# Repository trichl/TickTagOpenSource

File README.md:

# I Repository Introduction
This repository contains the entire production-ready design (hardware, software, user interface, 3D-printable housing, assembly instructions) of the open-source TickTag GPS logger.

# II Hardware Production
* See sub folder [TickTagHardware](TickTagHardware)
* Schematics (.sch) and boards (.brd) are designed in Autodesk Eagle 9.5.2
* PCBs were produced and assembled by [PCBWay](https://www.pcbway.com) (production-ready Gerber files and PCBWay settings in [TickTagHardware/GerberProductionFiles](TickTagHardware/GerberProductionFiles))
* Production settings:
   * **REV3**: 24.9 x 10.5 mm, 2 layers, 0.15 mm thickness (flex), 0.35 mm min hole size, immersion gold (ENIG) surface finish (1U"), 0.06 mm min track spacing, 1 oz Cu finished copper, polyimide flex material

   * **REV4**: 23.61 x 10.06 mm, 2 layers, 0.2 mm thickness, 0.25 mm min hole size, immersion gold (ENIG) surface finish (1U"), tenting vias, 5/5 mil min track spacing, 1 oz Cu finished copper, FR-4 TG150 material

   * **User interface board**: 66.4 x 17.8 mm, 2 layers, 1 mm thickness, 0.3 mm min hole size, immersion gold (ENIG) surface finish (1U"), tenting vias, 6/6 mil min track spacing, 1 oz Cu finished copper, FR-4 TG130 material
* Differences between REV3 and REV4:
   * 0.2 mm PCB instead of 0.15 mm (more robust)
   * PCB slots instead of pads for soldering LiPos directly to the PCB
   * New load switch (SiP32431DNP3-T1GE4), as the old load switch has long lead times
   * Reduced the footprint sizes of some of the capacitors and resistors from 0402 to 0201

# III Programming and Assembly

## IDE for Software Development (Windows)
* Atmel Studio 7.0: https://www.microchip.com/en-us/tools-resources/develop/microchip-studio
* Programming language: C / C++

## Android App
* Developed in Android Studio 3.5.1: https://developer.android.com/studio

## Using an Arduino Nano for Flashing
* Follow the instructions on https://github.com/ElTangas/jtag2updi
* The 4.7k resistor is already integrated on the user interface board and does not need to be added
* Alternatively software can be flashed with the official Atmel-ICE: https://www.microchip.com/en-us/development-tool/ATATMEL-ICE

## Flashing the Firmware
Flashing should be done before soldering a battery to the tag.

1. Check if the yellow jumper (E) connects "1" and "2" ("ldo")
2. Gently click the tag on the user interface board (without battery attached to it) (A), mind the correct orientation of the tag
3. Connect D6 of the Arduino Nano to the UPDI pin of the user interface board (or use an Atmel-ICE instead of an Arduino Nano)
4. Connect the user interface board to a computer (red LED turns on) (G), connect the Arduino Nano to the same computer
5. Slide the UPDI button on the user interface board (H) to ON
6. Go to [TickTagProgramming/avrdude](TickTagProgramming/avrdude), open ScriptWriteFuses_ATTINY1626.bat (or ScriptWriteFuses_ATTINY1616.bat, if you use the 1616) with a text editor and enter the COM port of the Arduino Nano on your computer
7. Execute ScriptWriteFuses_ATTINY1626.bat to write the configuration fuses of the ATTINY.
( It may be possible that executing the script raises an error ie. missing dll file. In this case, try to download and install WinAVR [here](https://sourceforge.net/projects/winavr/) )
8. Open Atmel Studio 7.0 and load the project [TickTagSoftwareBurst](TickTagSoftwareBurst) (you might need to setup the project first, and set the current device to ATtiny1626)
9.  
    1.  Configure the ATTINY programming via Arduino Nano under Tools -> External Tools
    2.  To choose the command, select the three dots and find the location of the TickTagOpenSource repository. Then navigate to TickTagProgramming\avrdude\bin and select avrdude.exe
    3.  For the Arguments: "-P COM7 -c jtag2updi -p t1626 -U flash:w:$(ProjectDir)Debug\\$(TargetName).hex:i", COM7 needs to be replaced with the COM port of the Arduino Nano:

10. Press F7 to compile the firmware
11. Press Tools -> jtag2updi ATtiny1626 to flash the firmware

## Tag Assembly

* If the firmware is successfully flashed onto the microcontroller you can solder a battery to the TickTag battery terminals (plus and minus is written on the tag)
* No battery protection circuit is needed, the battery is protected by software
* You can use a glass fiber pen to roughen the LiPo tabs, which makes soldering of the aluminium tabs more easy (e.g., with a Laeufer 69119 pen)
* Keep the soldering work on the LiPo very short, otherwise the battery might be damaged due to high temperatures
* Keep the area below the TickTag as flat as possible, otherwise you might not be able to click the tag on the user interface board anymore

# IV Tag Manual

## Charging the Battery
**WARNING**: never connect the TickTag to the user interface board when the 3-pin jumper is set to "ldo", otherwise the LiPo will be damaged permanently. The battery can be recharged directly on the breakout board:

1. Check if the yellow jumper connects (E) "3" and "2" ("lipo")
2. Gently click the tag on the user interface board (with battery attached to it) (A), mind the correct orientation of the tag
3. Connect the USB connector to a computer or powerbank (red LED turns on) (G)
4. Slide the charge button on the user interface board (F) to the left (ON)
5. A green LED on the user interface board turns on and indicates that the battery is being charged
6. In case the tag was previously activated, it first needs to be deactivated:
   * Wait some minutes until battery is charged a bit
   * Press the white button (D) for 5 seconds to restart the tag and enter menue
   * Green LED on the tag will blink 5 times to indicate download mode and system restart
7. Wait until the green LED on the user interface board turns off (battery charged)
   * This can take hours (default charge current: 15 mA)
   * For example: an empty 30 mAh lipo battery needs 2 hours to be fully charged
   * For example an empty 120 mAh lipo battery needs 8 hours to be fully charged
8. The tag can be activated again (see chapter "Activation")
   * Warning: If the memory is full the tag can not be reactivated (data download necessary, see chapter "Data Download, Configuration and Memory Reset")

## Activation
* Prerequisites
   * The tags need to be connected to a charged lithium polymer battery (plus and minus pads on the tag are soldered to the battery)
   * If the battery voltage is too low, the tag won’t start (please charge the battery), see chapter "Charge Battery"
   * If the data memory is full, the tag won't start (please download the data and reset the memory), see chapter "Data Download, Configuration and Memory Reset"
   * Check the location of the green LED on the tag (it will give you visual feedback):

### Activation option 1: by a wire

1. Gently touch with one end of a conducting wire the ground connection where the battery minus is soldered to
2. Gently touch with the other end of the wire the hole marked with "A" (or "ST")
3. Once the tag starts blinking green, remove the wire immediately (should not take longer than 2 seconds)
4. The tag blinks 7 times to indicate that it’s activated, then waits for 700 ms and is blinking again to indicate battery status (1 time = battery low, 7 times = battery is full)
5. The green LED is located on the back side of the tag, so it's best to hold the breakout board sideways to see the blinking LED under the tag
6. If it doesn't blink at all: battery voltage might be low or the tag is already activated
7. If the tag blinks 5 times it entered download mode (was already activated), please wait a minute and start again from the beginning
8. The tag is activated and will start sampling GPS data after 10 seconds (default configuration, can be changed, see chapter "Data Download, Configuration and Memory Reset")

### Activation option 2: on breakout board

1. Locate the click connector on the tag (see picture above)
2. Take a look at the breakout board, do not connect the USB power connector (G) to the computer or phone (no external power needed for activation)
3. Gently click the tag on the user interface board (with battery attached to it) (A), mind the correct orientation of the tag
      * Take care of the correct orientation of the tag as shown in the photo, otherwise a short circuit might permanently damage the tag
4. Now press the white button (D) for two seconds until the tag starts to blink
      * Do not press the button longer than some seconds
      * The tag blinks 7 times to indicate that it’s activated, then waits for 700 ms and is blinking again to indicate battery status (1 time = battery low, 7 times = battery is full)
      * The green LED is located on the back side of the tag, so it's best to hold the breakout board sideways to see the blinking LED under the tag
      * If it doesn't blink at all: battery voltage might be low or the tag is already activated
      * If the tag blinks 5 times it entered download mode (was already activated), please wait a minute and start again from the beginning
5. The tag is activated and will start sampling GPS data after 10 seconds (default configuration, can be changed, see chapter "Data Download, Configuration and Memory Reset")

## After the Activation (Data Sampling)
* After the activation delay, the tag starts blinking green every second and tries to get the current time via GPS satellites. If it can’t obtain the time within 120 seconds, it will sleep for 15 minutes and will try again.
   * **IMPORTANT**: If blinking configuration is set to false the tag will completely stop blinking at all after getting the current UTC time
   * If you have configured the tag to only sample GPS at certain times:
       * **IMPORTANT**: Before attaching the tag to the animal (e.g., the day before): go outside, activate the tag, wait until it starts blinking, wait until the green LED stays on for 2 seconds (tag got the time and went to sleep mode).
* The tag samples GPS data (continuously or from time to time, depending on the configuration)
* The module deactivates itself if the battery voltage is low (default configuration: 3.3V) or if the memory is full (maximum 13,100 fixes)

## On-Animal Mounting
* **IMPORTANT**: The small antenna of the TickTag is disturbed by any electrically conducting material nearby, so keep the antenna away from other tags, VHF/UHF tags, batteries, screws or similar materials (at least 5 cm).
* **IMPORTANT**: The antenna can easily break if bent too strong. Try to protect the antenna with a 3D-printed housing (for example with ASA material).
* **IMPORTANT**: The battery needs to be located behind the tag (see picture below), never under the tag, as it will disturb the antenna.
* **IMPORTANT**: Mount the tag on the flat side (connector facing down, top side with antenna facing the sky). The photo shows the top side that should face the sky:

* **IMPORTANT**: Do not glue anything on the connector that can't be removed, otherwise data cannot be downloaded (Bostik Blu Tack is a glue that can be easily removed afterwards):

## Data Download, Configuration and Memory Reset

1. Choose a serial software
   * **Option 1**: Download a serial program for your computer
       * For example (Windows 10): Termite: https://www.compuphase.com/software_termite.htm (see screenshot above for configuration)
       * For example (Windows 10): MobaXTerm: https://mobaxterm.mobatek.net/ (see screenshot above for configuration)
       * The Arduino Serial Monitor also works fine
   * **Option 2**: Use the TickTag Android app [TickTagAndroidApp](TickTagAndroidApp) and an USB OTG adapter to connect the breakout board with the phone
2. The battery needs to be connected (soldered) to the tag
3. Check if the yellow jumper connects (E) "3" and "2" ("lipo")
4. Gently click the tag on the user interface board (with battery attached to it) (A), mind the correct orientation of the tag
5. Connect the USB connector to a computer or Android phone (red LED turns on) (G)
6. Slide the charge button on the user interface board (F) to the left (ON) to charge the battery while downloading data (not mandatory, but recommended)
7. **For option 1**: Open the serial program on your computer with following settings:
   * COM port: select the CP2104N COM port from the list
   * Baud rate: 9600
   * Default serial settings (8 data bits, 1 stop bit, no parity)
8. Click on CONNECT in your serial program or the Android app
9. Press the download button (D) for 5 seconds (not longer) until the green LED on the tag blinks for 5 times
10. Data download is shown in your serial program (in CSV format)
11. After the download the tag shows a little menu for configuration
       * Data download might take some minutes (if memory is full)
       * Data download can be interrupted by pressing the download button once (short), data will not be deleted
12. In the command line of your serial program enter "1" and press return to reset the memory (when using the Android app: press the "Reset memory" button)
13. The tag will confirm that the memory is now empty
14. The tag will restart into the activation state after some time (waiting on tag activation, see chapter "Activation")

Example data output of the serial program (or Android app):

```
---TICK-TAG---
*START MEMORY*
UVs: 0, TOs: 0/0, ErrorsOrGF: 0, TTFF: 68
Fixes: 10, Avg. TTF: 11 s, Avg. HDOP (x10): 16
count,timestamp,lat,lon
1,1635235981,47.74340,8.99910
2,1635236130,47.74346,8.99922
3,1635236352,47.74340,8.99889
4,1635236506,47.74327,8.99894
5,1635236682,47.74336,8.99879
6,1635238092,47.74340,8.99824
7,1635238313,47.74304,8.99896
8,1635238411,47.74329,8.99883
9,1635238511,47.74332,8.99878
10,1635238610,47.74325,8.99881
*END MEMORY*
V201, ID: 30-2509, 3533mV, 01b
SETTINGS:
- Min voltage: 3300 mV
- Frequency: 90 s
- Min HDOP (x10): 30
- Activation delay: 60 s
- Geofencing: 0
- Burst duration: 0 s
- Time: 8:00 - 14:00 UTC

0 Read memory
1 Reset memory
2 Set min. voltage
3 Set frequency
4 Set accuracy
5 Set activation delay
6 Set times
7 Toggle geofencing ON/OFF
8 Set burst duration
9 Exit
```

## Configuration Parameters
* **Read memory**: printing all stored GPS fixes as CSV-compatible list (count, timestamp in UTC, latitude, longitude)
* **Reset memory**: deleting all stored GPS fixes
* **Min. voltage (3000 - 4250, in mV)**: recording is stopped when battery voltage (open-circuit, no load) drops below that threshold
* **Frequency (1 - 16382, in s)**: GPS fix attempt frequency, between 1 and 5 s the TickTag keeps the GPS module constantly powered and puts the device in fitness low power mode
* **Accuracy (1 - 250, HDOP x 10)**: HDOP value (times 10, 30 = 3.0) that tries to be achieved within 9 seconds after getting the first positional estimate
* **Activation delay (10 - 16382, in s)**: delay after activation before the tag starts recording data
* **Sampling times (0000 - 2359, time within day)**: daily recording time window
* **Geo-fencing (true/false)**: if set to true the first GPS fix becomes the home location and only fixes outside a 300 m radius are stored (10 min hibernation afterwards)
* **Blinking (true/false)**: if set to true the tag blinks every second when GPS is active

## Default Configuration
* After flashing the firmware the default configuration is set to:
* **Min. voltage (3000 - 4250, in mV)**: 3000
* **Frequency (1 - 16382, in s)**: 30
* **Accuracy (1 - 250, HDOP x 10)**: 30
* **Activation delay (10 - 16382, in s)**: 10
* **Sampling times (0000 - 2359, time within day)**: always on
* **Geo-fencing (true/false)**: false
* **Blinking (true/false)**: false

## State Machine

# V Data Compression Algorithm
GPS data is stored on the 128 kByte EEPROM with a lossless compression algorithm. GPS positions are stored with 5 decimal places (accuracy: 1.11 m).

* **Latitute (A)**: stored in 25 Bit (unsigned): compressedLatitude = (latitude * 100000) + 9000000
* **Longitude (B)**: stored in 26 Bit (unsigned): compressedLongitude = (longitude * 100000) + 18000000
* **Timestamp (C)**: stored in 29 Bit  (unsigned): compressedTimestamp = timestamp - 1618428394
* Storage pattern of Bits: **AAAAAAAA AAAAAAAA AAAAAAAA ABBBBBBB BBBBBBBB BBBBBBBB BBBCCCCC CCCCCCCC CCCCCCCC CCCCCCCC**
* Total length: 10 Byte per GPS fix

# VI 3D-printed Housings
* Check [TickTag3DPrints](TickTag3DPrints) for .STL files (designed in Fusion 360)
* Housings were printed with ASA filament on a Prusa Mini (0.4 mm nozzle)
* PrusaSlider 2.2.0 settings: 0.45 mm extrusion width, 0.10 mm DETAIL settings

# VII Data
* Check [TickTagData](TickTagData) for data results

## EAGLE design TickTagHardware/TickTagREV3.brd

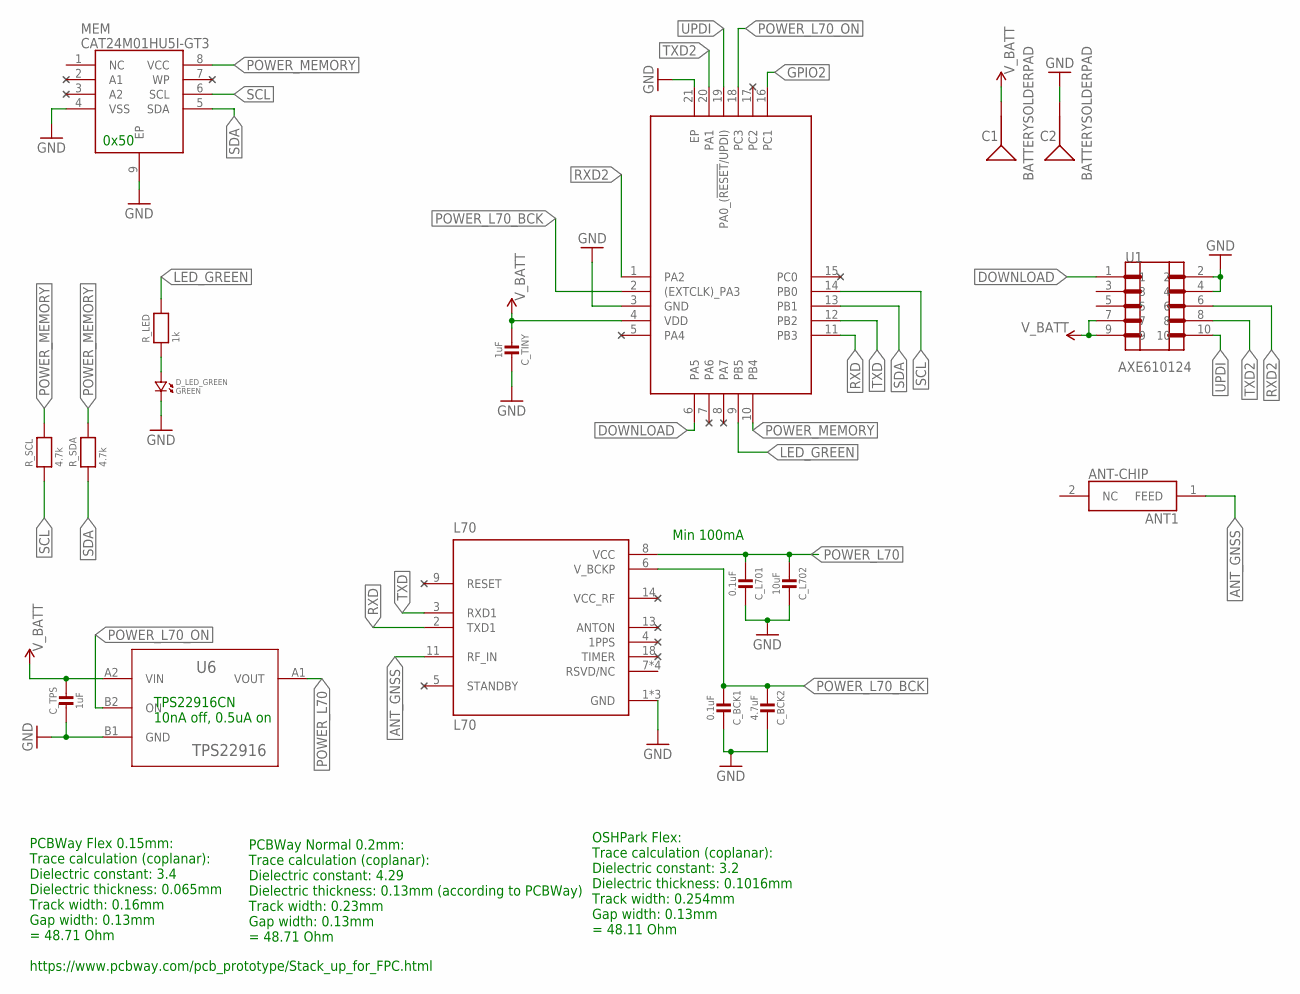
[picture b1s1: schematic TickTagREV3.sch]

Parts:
ANT-CHIP: ANT1; SAMACSYS_PARTS_1575AT43A0040E
ATTINY: ATTINY1616-MFR; QFN40P300X300X90-21N
C1, C2: BATTERYSOLDERPAD
C_BCK1: 0.1uF; MICROBUILDER__0402MP
C_BCK2: 4.7uF; MICROBUILDER__0402MP
C_L701: 0.1uF; MICROBUILDER__0402MP
C_L702: 10uF; MICROBUILDER__0402MP
C_TINY: 1uF; MICROBUILDER__0402MP
C_TPS: 1uF; MICROBUILDER__0402MP
D_LED_GREEN: GREEN; CMONR_STANDARDPARTS_0402.LED
L70: L70; XCVR_L70
MEM: CAT24M01HU5I-GT3; SON50P300X200X55-9N
R_LED: 1k; MICROBUILDER__0402MP
R_SCL: 4.7k; MICROBUILDER__0402MP
R_SDA: 4.7k; MICROBUILDER__0402MP
U1: AXE610124
U6: TPS22916

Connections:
ANT_GNSS: ANT-CHIP.1 (FEED), L70.11 (RF_IN)
DOWNLOAD: ATTINY.6 (PA5), U1.1
GND: ATTINY.3 (GND), ATTINY.21 (EP), C2.1, C_BCK1.1, C_BCK2.1, C_L701.1, C_L702.1, C_TINY.1, C_TPS.2, D_LED_GREEN.P$2 (2), L70.1 (GND), L70.10 (GND), L70.12 (GND), MEM.4 (VSS), MEM.9 (EP), U1.2, U1.4, U6.B1 (GND)
GPIO2: ATTINY.16 (PC1)
LED_GREEN: ATTINY.9 (PB5), R_LED.2
unnamed: D_LED_GREEN.P$1 (1), R_LED.1
POWER_L70: C_L701.2, C_L702.2, L70.8 (VCC), U6.A1 (VOUT)
POWER_L70_BCK: ATTINY.2 ((EXTCLK)_PA3), C_BCK1.2, C_BCK2.2, L70.6 (V_BCKP)
POWER_L70_ON: ATTINY.18 (PC3), U6.B2 (ON)
POWER_MEMORY: ATTINY.10 (PB4), MEM.8 (VCC), R_SCL.2, R_SDA.2
RXD: ATTINY.11 (PB3), L70.2 (TXD1)
RXD2: ATTINY.1 (PA2), U1.6
SCL: ATTINY.14 (PB0), MEM.6 (SCL), R_SCL.1
SDA: ATTINY.13 (PB1), MEM.5 (SDA), R_SDA.1
TXD: ATTINY.12 (PB2), L70.3 (RXD1)
TXD2: ATTINY.20 (PA1), U1.8
UPDI: ATTINY.19 (PA0_(!RESET!/UPDI)), U1.10
V_BATT: ATTINY.4 (VDD), C1.1, C_TINY.2, C_TPS.1, U1.7, U1.9, U6.A2 (VIN)

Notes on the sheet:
0x50
Min 100mA
TPS22916CN 10nA off, 0.5uA on
OSHPark Flex: Trace calculation (coplanar): Dielectric constant: 3.2 Dielectric thickness: 0.1016mm Track width: 0.254mm Gap width: 0.13mm = 48.11 Ohm
PCBWay Flex 0.15mm: Trace calculation (coplanar): Dielectric constant: 3.4 Dielectric thickness: 0.065mm Track width: 0.16mm Gap width: 0.13mm = 48.71 Ohm https://www.pcbway.com/pcb_prototype/Stack_up_for_FPC.html
PCBWay Normal 0.2mm: Trace calculation (coplanar): Dielectric constant: 4.29 Dielectric thickness: 0.13mm (according to PCBWay) Track width: 0.23mm Gap width: 0.13mm = 48.71 Ohm

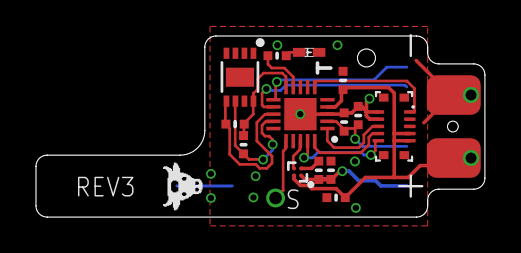
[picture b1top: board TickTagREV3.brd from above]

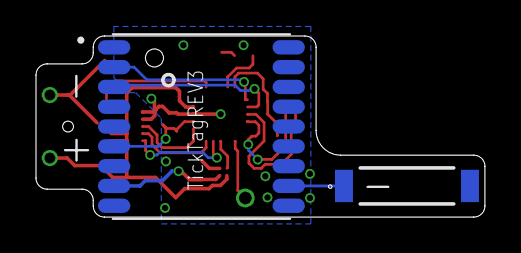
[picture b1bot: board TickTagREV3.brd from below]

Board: 2 copper layers, 24.9 x 10.1 mm, 18 parts (2 on the bottom side), 17 nets.

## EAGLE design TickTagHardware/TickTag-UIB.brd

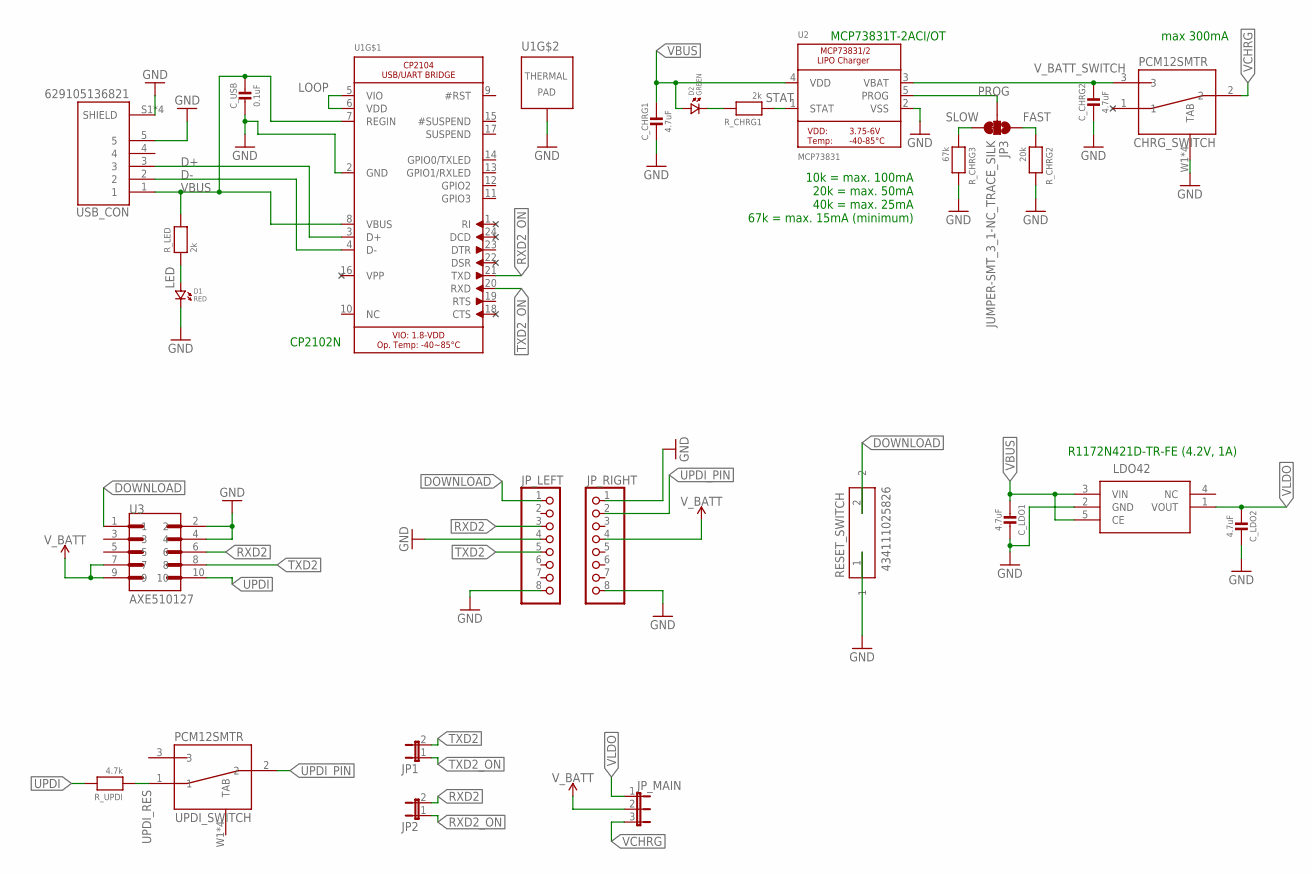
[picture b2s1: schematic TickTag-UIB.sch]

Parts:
CHRG_SWITCH: PCM12SMTR
C_CHRG1, C_CHRG2: 4.7uF; MICROBUILDER__0402MP
C_LDO1, C_LDO2: 4.7uF; MICROBUILDER__0402MP
C_USB: 0.1uF; MICROBUILDER__0402MP
D1: RED; CMONR_STANDARDPARTS_0402.LED
D2: GREEN; CMONR_STANDARDPARTS_0402.LED
JP1, JP2: JP1E; JP1
JP3: JUMPER-SMT_3_1-NC_TRACE_SILK; SMT-JUMPER_3_1-NC_TRACE_SILK
JP_LEFT: PINHD-1X8BIG; 1X08-BIG
JP_MAIN: JP2E; JP2
JP_RIGHT: PINHD-1X8BIG; 1X08-BIG
LDO42: R1172N421D-TR-FE
RESET_SWITCH: 434111025826
R_CHRG1: 2k; MICROBUILDER__0402MP
R_CHRG2: 20k; MICROBUILDER__0402MP
R_CHRG3: 67k; MICROBUILDER__0402MP
R_LED: 2k; MICROBUILDER__0402MP
R_UPDI: 4.7k; MICROBUILDER__0402MP
U1: CP2104_MICROBUILDER_CP2104; CP2104_MICROBUILDER_QFN24_4MM_SMSC
U2: MCP73831; MICROBUILDER_SOT23-5
U3: AXE510127
UPDI_SWITCH: PCM12SMTR
USB_CON: 629105136821; WE_629105136821

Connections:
D+: U1.3 (D+), USB_CON.3
D-: U1.4 (D-), USB_CON.2
DOWNLOAD: JP_LEFT.1, RESET_SWITCH.2, U3.1
FAST: JP3.1, R_CHRG2.1
GND: CHRG_SWITCH.W1 (TAB), CHRG_SWITCH.W2 (TAB), CHRG_SWITCH.W3 (TAB), CHRG_SWITCH.W4 (TAB), C_CHRG1.2, C_CHRG2.2, C_LDO1.1, C_LDO2.1, C_USB.2, D1.P$2 (2), JP_LEFT.4, JP_LEFT.8, JP_RIGHT.1, JP_RIGHT.8, LDO42.2 (GND), RESET_SWITCH.1, R_CHRG2.2, R_CHRG3.2, U1.2 (GND), U1.THERM (TP), U2.2 (VSS), U3.2, U3.4, USB_CON.5, USB_CON.S1 (SHIELD), USB_CON.S2 (SHIELD), USB_CON.S3 (SHIELD), USB_CON.S4 (SHIELD)
LED: D1.P$1 (1), R_LED.1
LOOP: U1.5 (VIO), U1.6 (VDD)
PROG: JP3.2, U2.5 (PROG)
RXD2: JP2.2, JP_LEFT.3, U3.6
RXD2_ON: JP2.1, U1.21 (TXD)
SLOW: JP3.3, R_CHRG3.1
STAT: R_CHRG1.1, U2.1 (STAT)
STAT_BTW: D2.P$2 (2), R_CHRG1.2
TXD2: JP1.2, JP_LEFT.5, U3.8
TXD2_ON: JP1.1, U1.20 (RXD)
UPDI: R_UPDI.2, U3.10
UPDI_PIN: JP_RIGHT.2, UPDI_SWITCH.2
UPDI_RES: R_UPDI.1, UPDI_SWITCH.1
VBUS: C_CHRG1.1, C_LDO1.2, C_USB.1, D2.P$1 (1), LDO42.3 (VIN), LDO42.5 (CE), R_LED.2, U1.7 (REGIN), U1.8 (VBUS), U2.4 (VDD), USB_CON.1
VCHRG: CHRG_SWITCH.2, JP_MAIN.3
VLDO: C_LDO2.2, JP_MAIN.1, LDO42.1 (VOUT)
V_BATT: JP_MAIN.2, JP_RIGHT.4, U3.7, U3.9
V_BATT_SWITCH: CHRG_SWITCH.3, C_CHRG2.1, U2.3 (VBAT)

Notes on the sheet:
10k = max. 100mA 20k = max. 50mA 40k = max. 25mA 67k = max. 15mA (minimum)
max 300mA
CP2102N
MCP73831T-2ACI/OT
R1172N421D-TR-FE (4.2V, 1A)

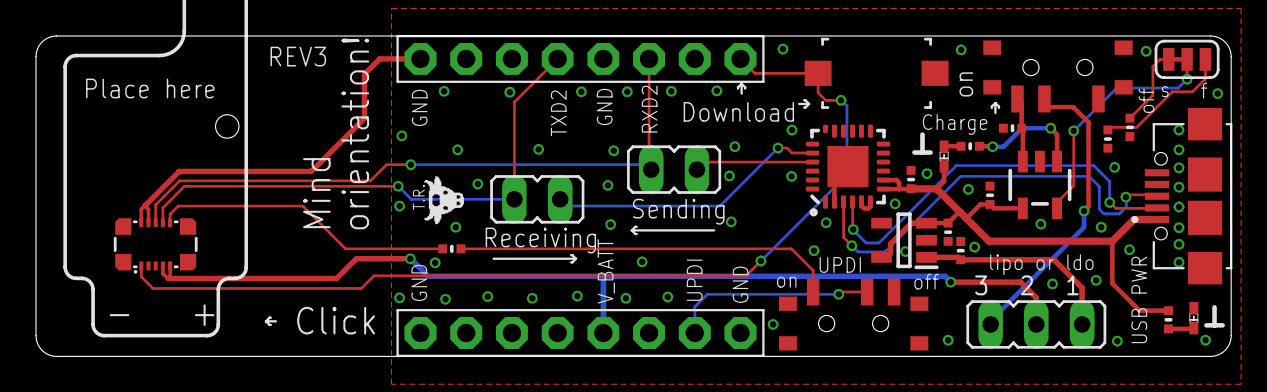
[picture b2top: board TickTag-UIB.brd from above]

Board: 2 copper layers, 66.4 x 17.8 mm, 26 parts (0 on the bottom side), 23 nets.

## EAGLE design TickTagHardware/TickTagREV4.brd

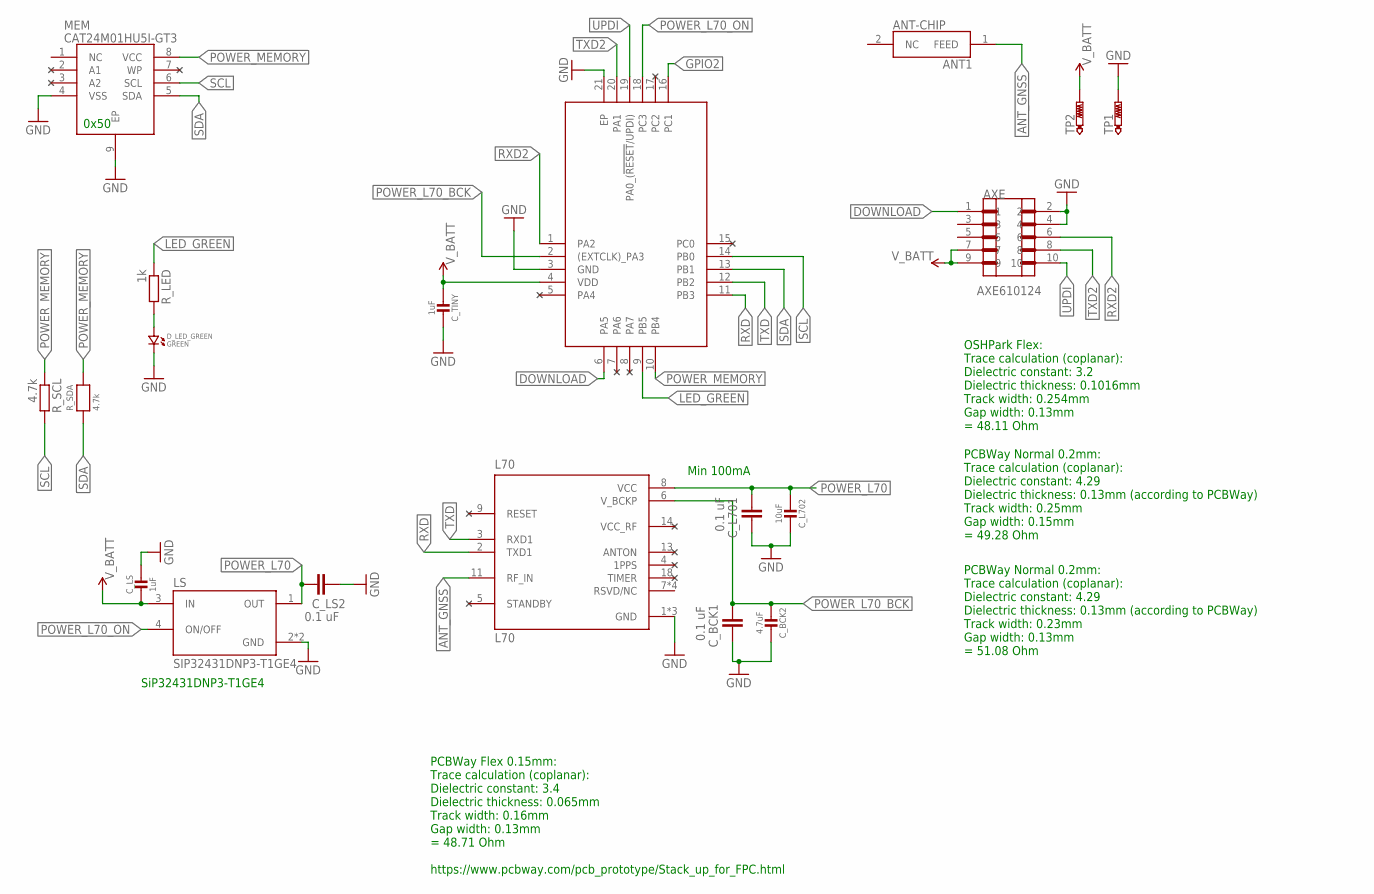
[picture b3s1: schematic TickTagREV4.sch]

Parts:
ANT-CHIP: ANT1; SAMACSYS_PARTS_1575AT43A0040E
ATTINY: ATTINY1616-MFR; QFN40P300X300X90-21N
AXE: AXE610124
C_BCK1: 0.1 uF; C0201
C_BCK2: 4.7uF; MICROBUILDER__0402MP
C_L701: 0.1 uF; C0201
C_L702: 10uF; MICROBUILDER__0402MP
C_LS: 1uF; MICROBUILDER__0402MP
C_LS2: 0.1 uF; C0201
C_TINY: 1uF; MICROBUILDER__0402MP
D_LED_GREEN: GREEN; CMONR_STANDARDPARTS_0402.LED
L70: L70; XCVR_L70
LS: SIP32431DNP3-T1GE4; SON50P120X160X60-5N
MEM: CAT24M01HU5I-GT3; SON50P300X200X55-9N
R_LED: 1k; R0201
R_SCL: 4.7k; R0201
R_SDA: 4.7k; MICROBUILDER__0402MP
TP1, TP2: PTR1TP13SQ; TP13SQ

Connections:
ANT_GNSS: ANT-CHIP.1 (FEED), L70.11 (RF_IN)
DOWNLOAD: ATTINY.6 (PA5), AXE.1
GND: ATTINY.3 (GND), ATTINY.21 (EP), AXE.2, AXE.4, C_BCK1.2, C_BCK2.1, C_L701.2, C_L702.1, C_LS.1, C_LS2.2, C_TINY.1, D_LED_GREEN.P$2 (2), L70.1 (GND), L70.10 (GND), L70.12 (GND), LS.2 (GND), LS.5 (GND), MEM.4 (VSS), MEM.9 (EP), TP1.TP
GPIO2: ATTINY.16 (PC1)
LED_GREEN: ATTINY.9 (PB5), R_LED.1
unnamed: D_LED_GREEN.P$1 (1), R_LED.2
POWER_L70: C_L701.1, C_L702.2, C_LS2.1, L70.8 (VCC), LS.1 (OUT)
POWER_L70_BCK: ATTINY.2 ((EXTCLK)_PA3), C_BCK1.1, C_BCK2.2, L70.6 (V_BCKP)
POWER_L70_ON: ATTINY.18 (PC3), LS.4 (ON/OFF)
POWER_MEMORY: ATTINY.10 (PB4), MEM.8 (VCC), R_SCL.1, R_SDA.2
RXD: ATTINY.11 (PB3), L70.2 (TXD1)
RXD2: ATTINY.1 (PA2), AXE.6
SCL: ATTINY.14 (PB0), MEM.6 (SCL), R_SCL.2
SDA: ATTINY.13 (PB1), MEM.5 (SDA), R_SDA.1
TXD: ATTINY.12 (PB2), L70.3 (RXD1)
TXD2: ATTINY.20 (PA1), AXE.8
UPDI: ATTINY.19 (PA0_(!RESET!/UPDI)), AXE.10
V_BATT: ATTINY.4 (VDD), AXE.7, AXE.9, C_LS.2, C_TINY.2, LS.3 (IN), TP2.TP

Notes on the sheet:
0x50
Min 100mA
OSHPark Flex: Trace calculation (coplanar): Dielectric constant: 3.2 Dielectric thickness: 0.1016mm Track width: 0.254mm Gap width: 0.13mm = 48.11 Ohm
PCBWay Flex 0.15mm: Trace calculation (coplanar): Dielectric constant: 3.4 Dielectric thickness: 0.065mm Track width: 0.16mm Gap width: 0.13mm = 48.71 Ohm https://www.pcbway.com/pcb_prototype/Stack_up_for_FPC.html
PCBWay Normal 0.2mm: Trace calculation (coplanar): Dielectric constant: 4.29 Dielectric thickness: 0.13mm (according to PCBWay) Track width: 0.23mm Gap width: 0.13mm = 51.08 Ohm
SiP32431DNP3-T1GE4
PCBWay Normal 0.2mm: Trace calculation (coplanar): Dielectric constant: 4.29 Dielectric thickness: 0.13mm (according to PCBWay) Track width: 0.25mm Gap width: 0.15mm = 49.28 Ohm

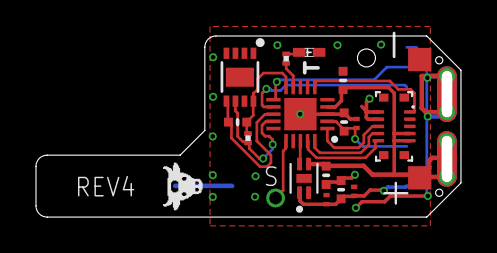
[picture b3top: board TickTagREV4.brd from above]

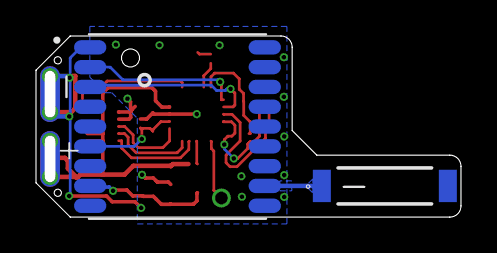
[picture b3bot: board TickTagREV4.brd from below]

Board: 2 copper layers, 23.6 x 10.1 mm, 19 parts (2 on the bottom side), 17 nets.

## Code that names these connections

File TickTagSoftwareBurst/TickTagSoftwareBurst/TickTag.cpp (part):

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
void deviceInitPins() {
	// OUTPUT = lowest setting
	PORTA.DIR = (INPUT_DIR << PIN0_bp)	// PA0: UPDI
	| (OUTPUT_DIR << PIN1_bp)			// PA1: TXD2
	| (OUTPUT_DIR << PIN2_bp)			// PA2: RXD2
	| (OUTPUT_DIR << PIN3_bp)			// PA3: POWER_L70_BCK
	| (OUTPUT_DIR << PIN4_bp)			// PA4: **UNUSED**
	| (INPUT_DIR << PIN5_bp)			// PA5: DOWNLOAD (NEW: changed from OUTPUT to INPUT)
	| (OUTPUT_DIR << PIN6_bp)			// PA6: TIMER
	| (OUTPUT_DIR << PIN7_bp);			// PA7: **UNUSED**	
	PORTB.DIR = (OUTPUT_DIR << PIN0_bp)	// PB0: SCL
	| (OUTPUT_DIR << PIN1_bp)			// PB1: SDA
	| (OUTPUT_DIR << PIN2_bp)			// PB2: TXD
	| (INPUT_DIR << PIN3_bp)			// PB3: RXD
	| (OUTPUT_DIR << PIN4_bp)			// PB4: POWER_MEMORY
	| (OUTPUT_DIR << PIN5_bp);			// PB5: LED_GREEN
	PORTC.DIR = (OUTPUT_DIR << PIN0_bp)	// PC0: **UNUSED**
	| (OUTPUT_DIR << PIN1_bp)			// PC1: GPIO2 (A/ST)
	| (OUTPUT_DIR << PIN2_bp)			// PC2: GPIO1
	| (OUTPUT_DIR << PIN3_bp);			// PC3: POWER_L70_ON
	
	#if defined (__AVR_ATtiny1626__)
	// doesn't work
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
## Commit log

2022-02-28 added images
2022-02-28 added hardware files
2022-03-02 added images for doc
2022-03-02 more images
2022-03-02 updated images
2022-03-02 resized images
2022-03-02 name change
2022-03-02 removed all
2022-03-02 added all images
2022-03-02 firmware upload
2022-03-02 uploaded android app
2022-06-08 added data from experiments
2022-09-20 added fuse writing for ATTINY1616 (alternative to 1626), removed confusing comments in schematics
2022-09-20 removed I2C bug when writing memory (causing long delay when writing)
2022-09-20 corrected BOMs
2024-01-31 Update README.md
    updates for specific issues
2024-03-04 New software versions
    Adding the new flashing method and software versions
2024-03-13 Added downloading tool
    Python tool for downloading and sorting data from Ticktags
2024-03-13 Documentation update
2024-03-13 Bug fix Unix systems
2024-06-21 added awesome housings for UIB and tags (made by mark holton)

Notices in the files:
parts and their libraries:
Wurth_Elektronik_Electromechanic_Switchs: Copyright: Würth Elektronik
SparkFun-Jumpers: Licensing: Creative Commons ShareAlike 4.0 International - https://creativecommons.org/licenses/by-sa/4.0
